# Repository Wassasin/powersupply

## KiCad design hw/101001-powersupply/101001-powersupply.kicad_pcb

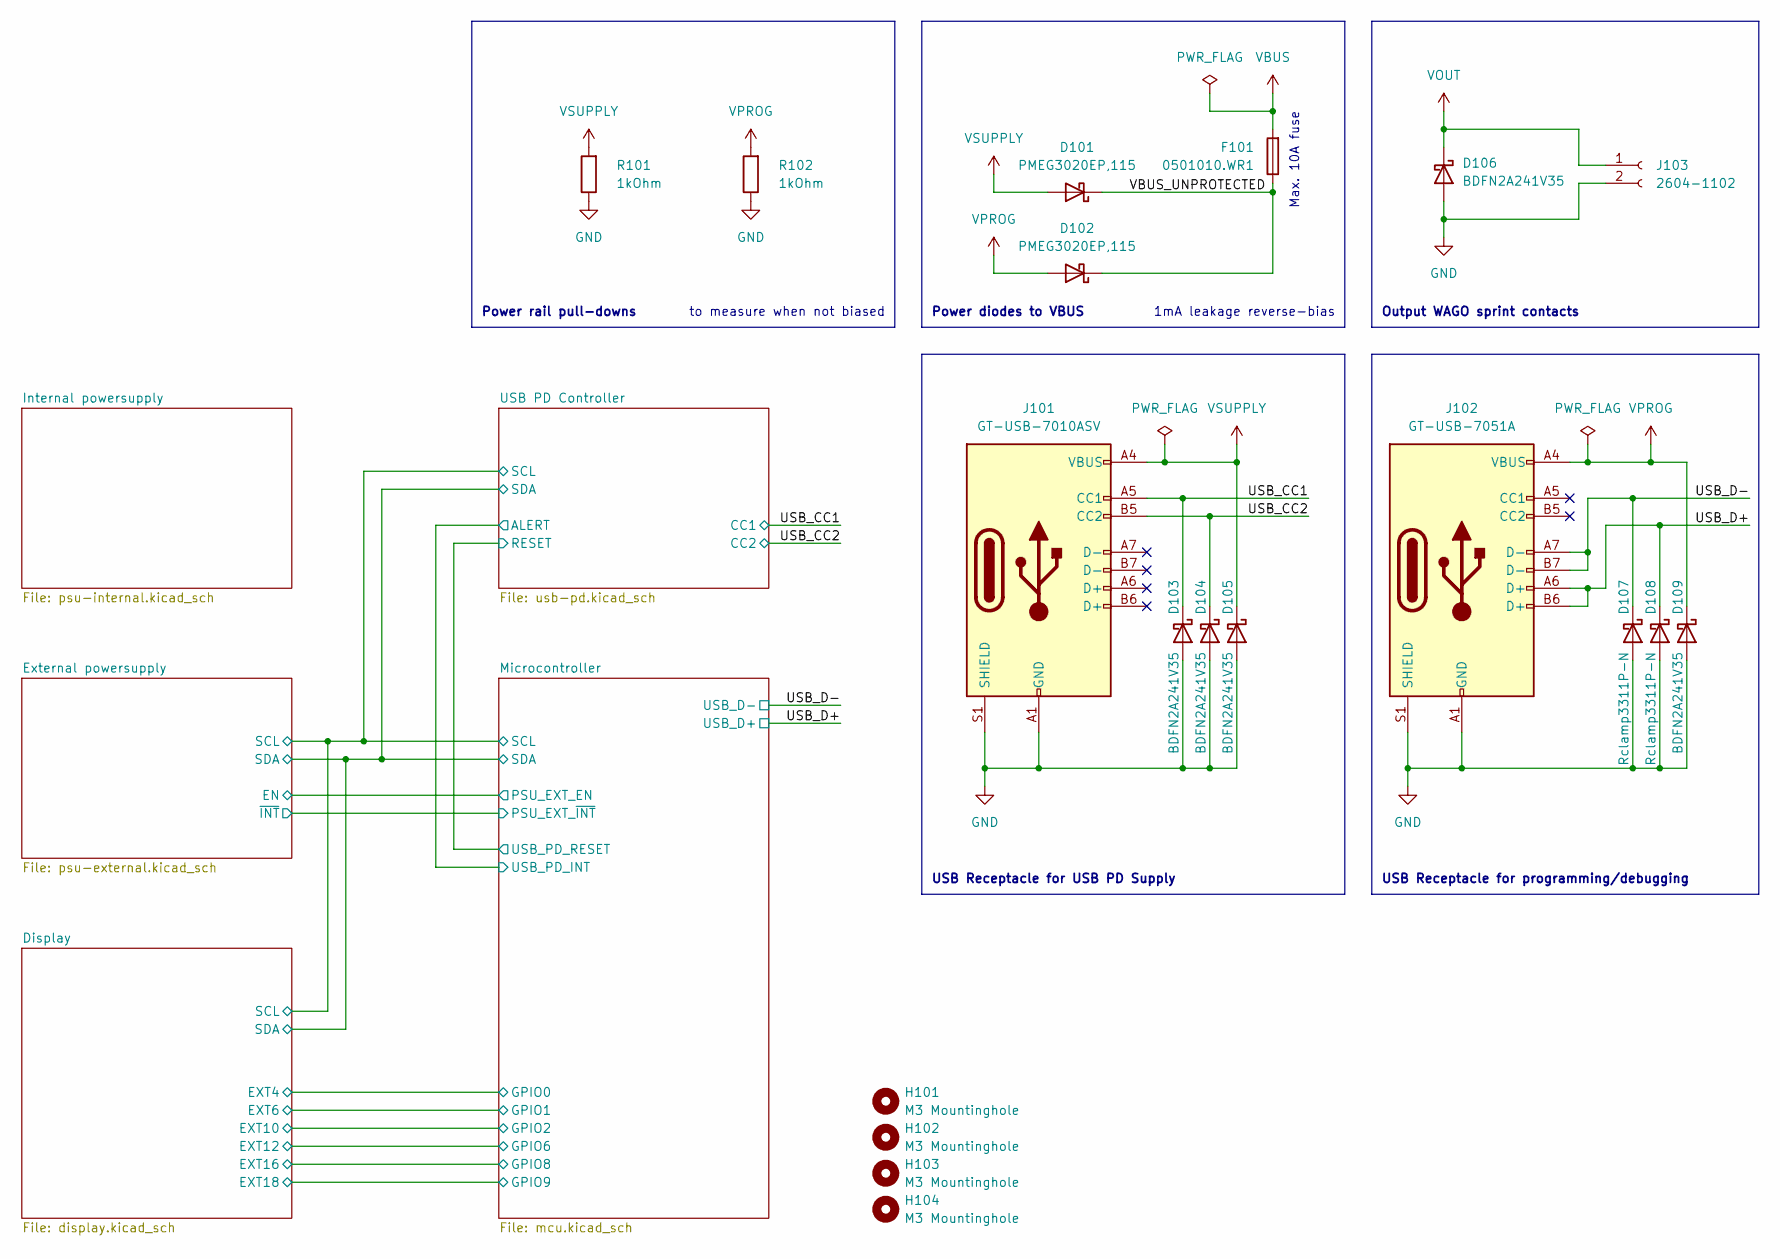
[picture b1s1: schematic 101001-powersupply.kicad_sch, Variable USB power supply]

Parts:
D101, D102: PMEG3020EP,115; D_SOD-128; LCSC C513108
D103, D104, D105, D106, D109: BDFN2A241V35; D_SOD-882; LCSC C406193
D107, D108: Rclamp3311P-N; D_SOD-882; LCSC C406234
F101: 0501010.WR1; Fuse_1206_3216Metric; LCSC C207003
H101, H102, H103, H104: M3 Mountinghole; MountingHole_3.2mm_M3
J101: GT-USB-7010ASV; USB_C_Receptacle_G-Switch_GT-USB-7010ASV; LCSC C2988369
J102: GT-USB-7051A; USB_C_Receptacle_G-Switch_GT-USB-7051x; LCSC C2843970
J103: 2604-1102; WAGO-2604-1102
R101, R102: 1kOhm; R_0402_1005Metric; LCSC C11702

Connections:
/USB_CC1: D103.1 (K), J101.A5 (CC1); also elsewhere on the board
/USB_CC2: D104.1 (K), J101.B5 (CC2); also elsewhere on the board
/USB_D+: D108.1 (K), J102.A6 (D+), J102.B6 (D+); also elsewhere on the board
/USB_D-: D107.1 (K), J102.A7 (D-), J102.B7 (D-); also elsewhere on the board
/VBUS_UNPROTECTED: D101.1 (K), D102.1 (K), F101.1
VBUS: F101.2; also elsewhere on the board
VOUT: D106.1 (K), J103.1; also elsewhere on the board
VPROG: D102.2 (A), D109.1 (K), J102.A4 (VBUS), J102.A9 (VBUS), J102.B4 (VBUS), J102.B9 (VBUS), R102.2; also elsewhere on the board
VSUPPLY: D101.2 (A), D105.1 (K), J101.A4 (VBUS), J101.A9 (VBUS), J101.B4 (VBUS), J101.B9 (VBUS), R101.2; also elsewhere on the board

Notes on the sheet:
to measure when not biased
Max. 10A fuse
Power rail pull-downs
USB Receptacle for programming/debugging
USB Receptacle for USB PD Supply
1mA leakage reverse-bias
Power diodes to VBUS
Output WAGO sprint contacts

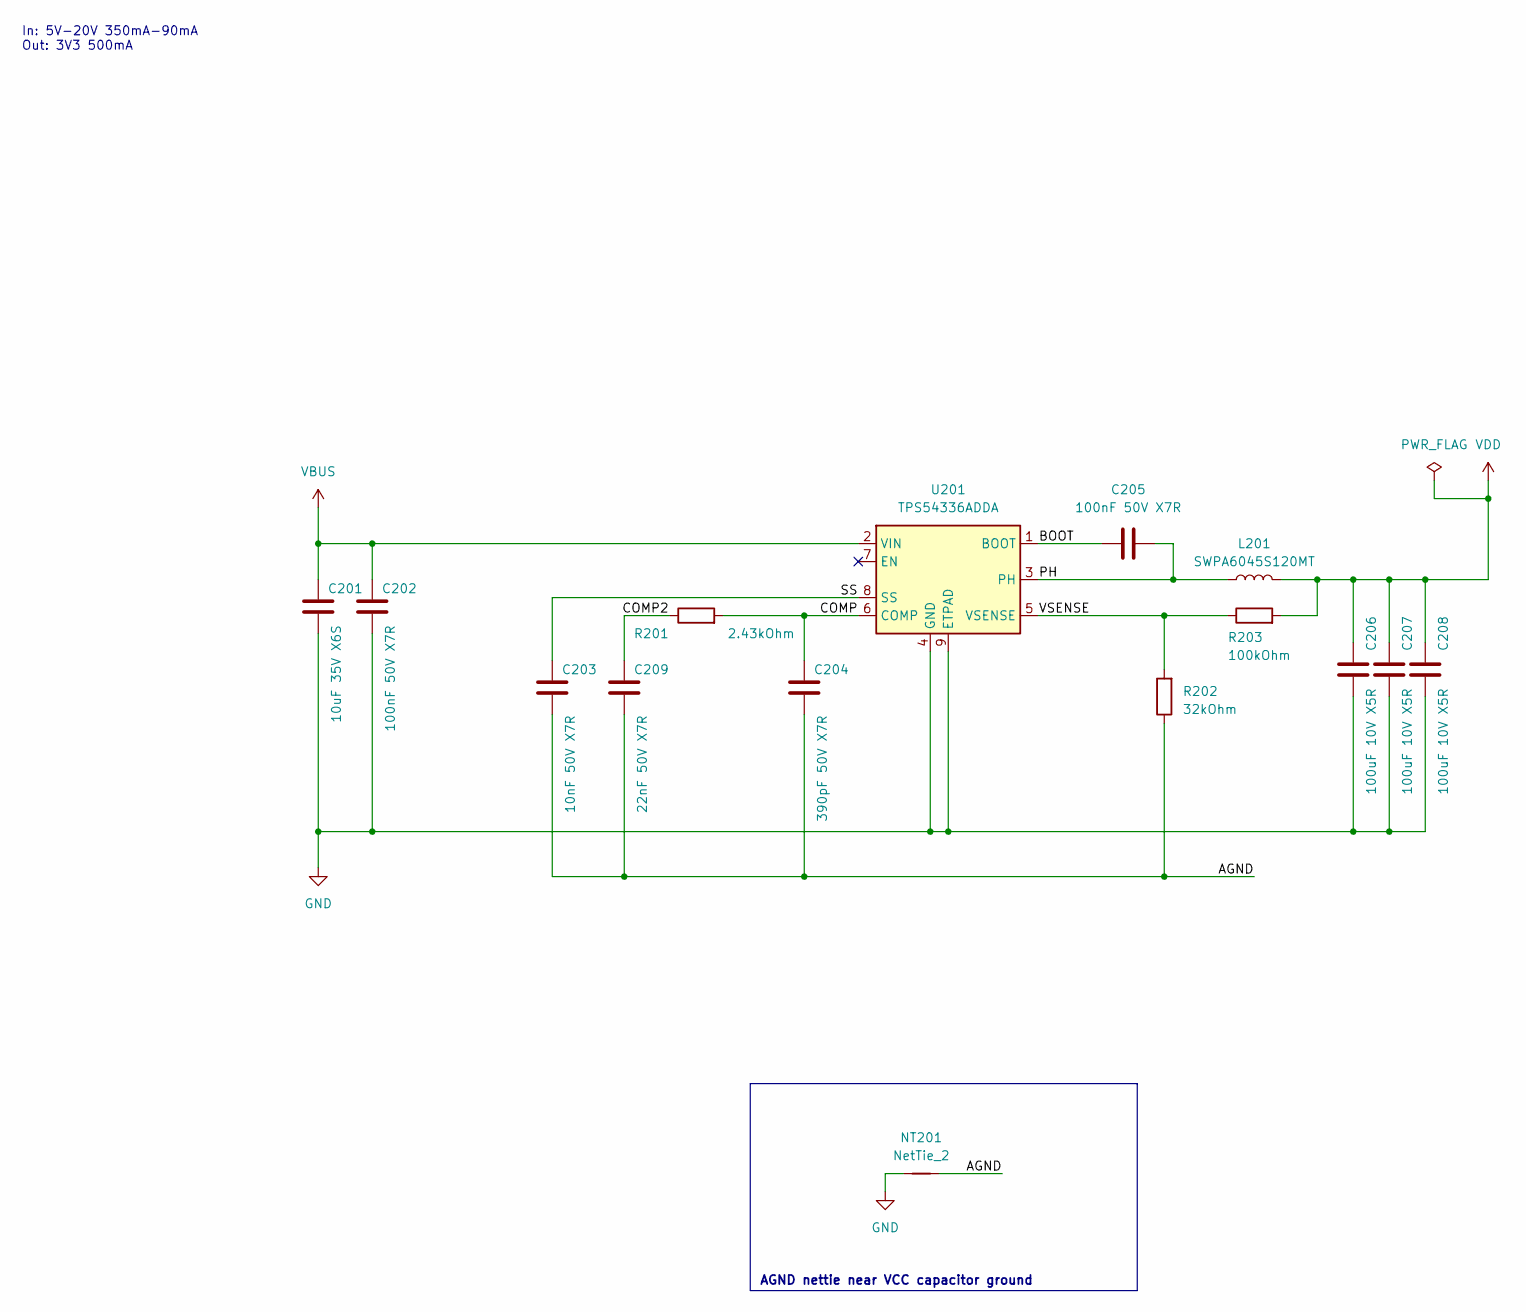
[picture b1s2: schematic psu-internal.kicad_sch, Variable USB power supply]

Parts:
C201: 10uF 35V X6S; C_0805_2012Metric; MPN GRM21BC8YA106KE11L; LCSC C469541
C202, C205: 100nF 50V X7R; C_0402_1005Metric; MPN CL05B104KB54PNC; LCSC C307331
C203: 10nF 50V X7R; C_0402_1005Metric; MPN CL05B103KB5NNNC; LCSC C15195
C204: 390pF 50V X7R; C_0402_1005Metric; MPN CC0402KRX7R9BB391; LCSC C114397
C206, C207, C208: 100uF 10V X5R; C_1206_3216Metric; MPN GRM31CR61A107ME05L; LCSC C312983
C209: 22nF 50V X7R; C_0402_1005Metric; MPN CL05B223KB5NNNC; LCSC C337699
L201: SWPA6045S120MT; L_Sunlord_SWPA6045S; MPN SWPA6045S120MT; LCSC C96951
NT201: NetTie_2; NetTie-2_SMD_Pad0.5mm
R201: 2.43kOhm; R_0402_1005Metric; LCSC C853891
R202: 32kOhm; R_0402_1005Metric; LCSC C11463
R203: 100kOhm; R_0402_1005Metric; LCSC C25741
U201: TPS54336ADDA; TI_SO-PowerPAD-8_ThermalVias; MPN TPS54336ADDA; LCSC C97668

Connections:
/Internal powersupply/AGND: C203.2, C204.2, C209.2, NT201.2, R202.1
/Internal powersupply/BOOT: C205.1, U201.1 (BOOT)
/Internal powersupply/COMP: C204.1, R201.2, U201.6 (COMP)
/Internal powersupply/COMP2: C209.1, R201.1
/Internal powersupply/PH: C205.2, L201.1, U201.3 (PH)
/Internal powersupply/SS: C203.1, U201.8 (SS)
/Internal powersupply/VSENSE: R202.2, R203.1, U201.5 (VSENSE)
VBUS: C201.1, C202.1, U201.2 (VIN); also elsewhere on the board
VDD: C206.1, C207.1, C208.1, L201.2, R203.2; also elsewhere on the board

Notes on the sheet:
In: 5V-20V 350mA-90mA Out: 3V3 500mA
AGND nettie near VCC capacitor ground

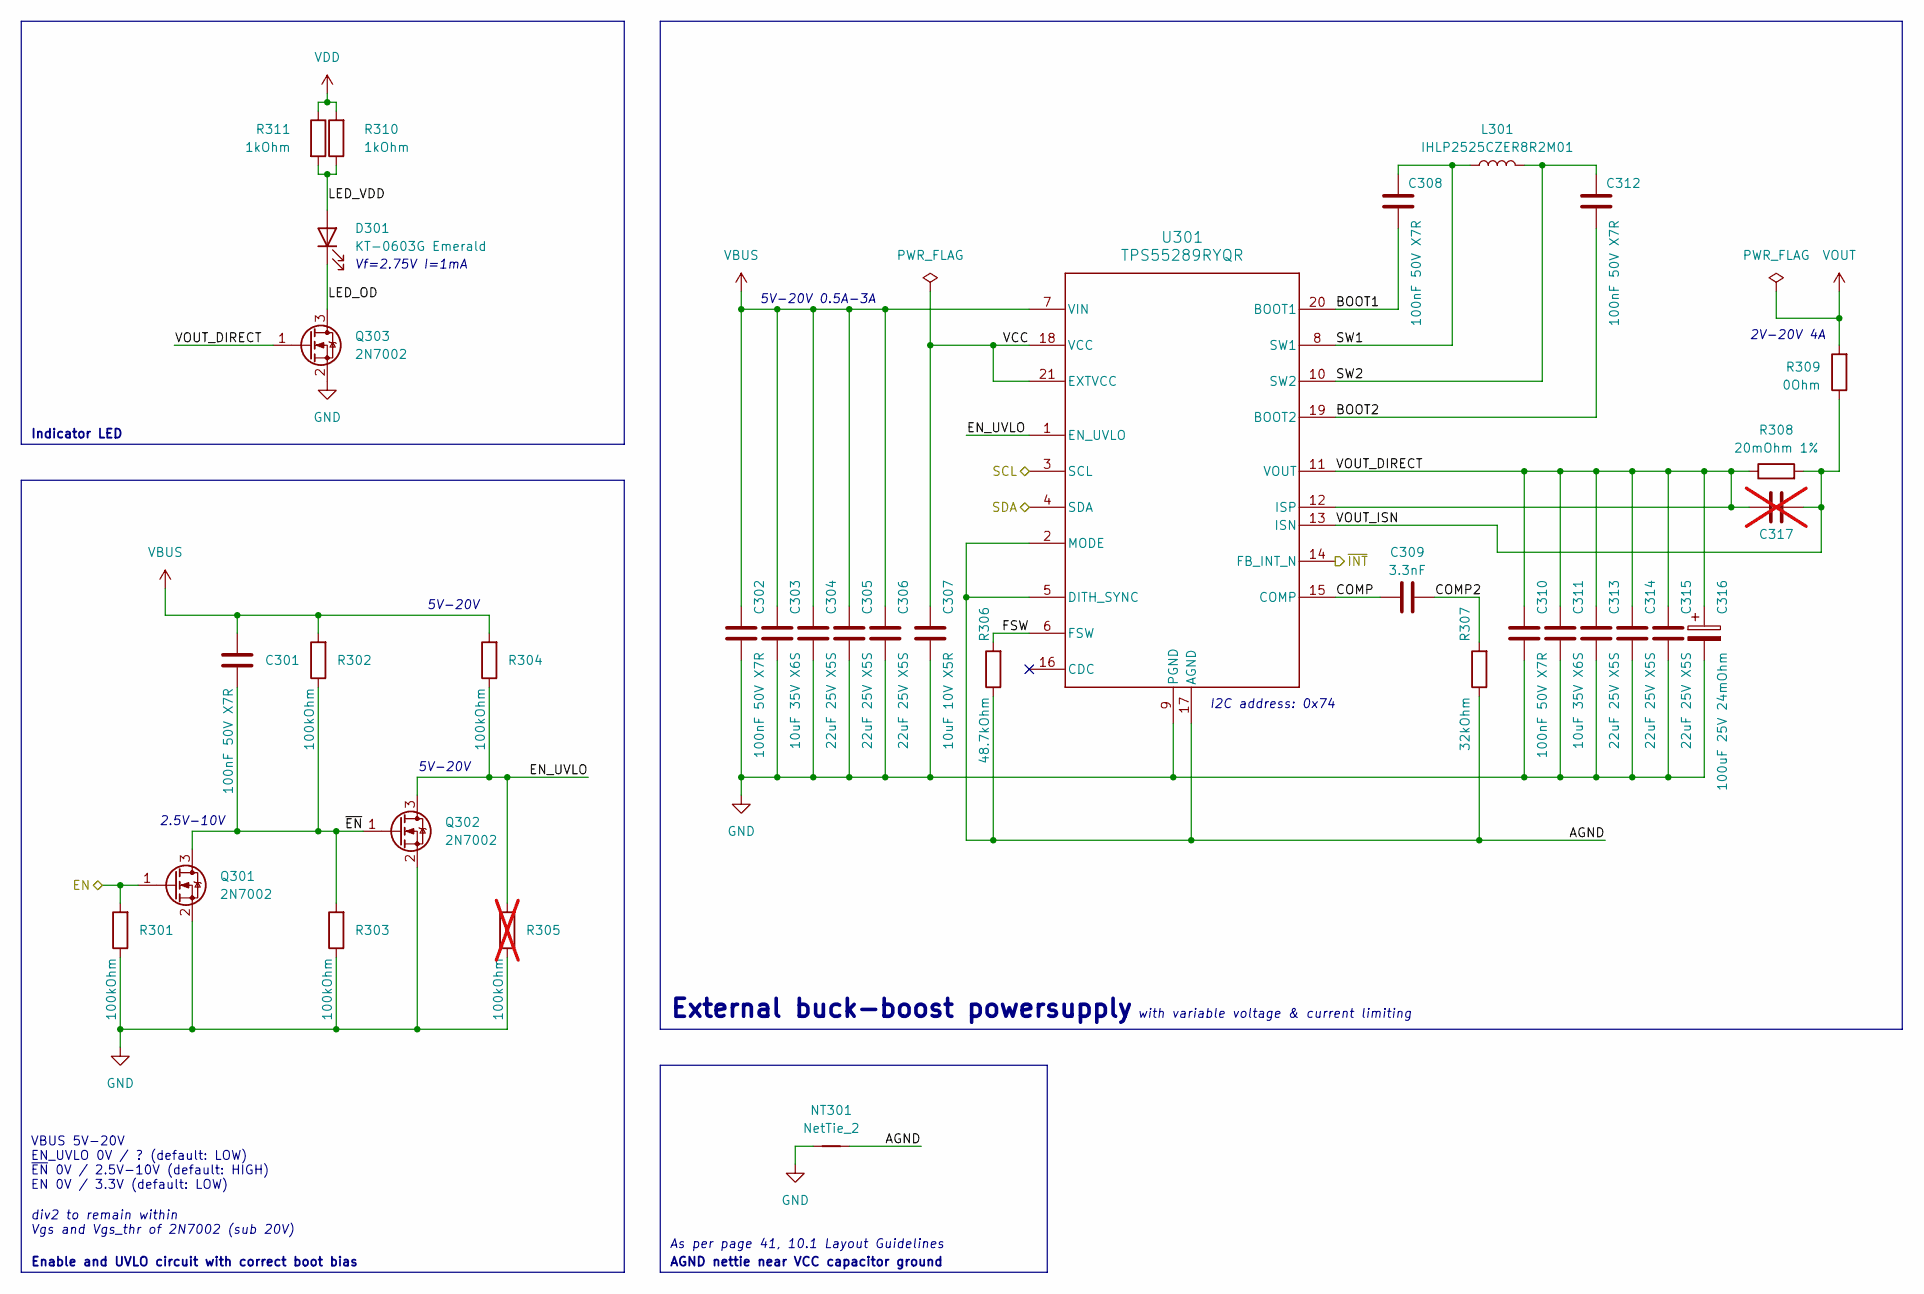
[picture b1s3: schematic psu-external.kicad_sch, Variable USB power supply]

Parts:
C301, C302, C308, C310, C312: 100nF 50V X7R; C_0402_1005Metric; MPN CL05B104KB54PNC; LCSC C307331
C303, C311: 10uF 35V X6S; C_0805_2012Metric; MPN GRM21BC8YA106KE11L; LCSC C469541
C304, C305, C306, C313, C314, C315: 22uF 25V X5S; C_1210_3225Metric; MPN GRM32ER71E226KE15L; LCSC C21397
C307: 10uF 10V X5R; C_0402_1005Metric; MPN GRM155R61A106ME11D; LCSC C408132
C309: 3.3nF; C_0402_1005Metric; MPN CC0402KRX7R9BB332; LCSC C107028
C316: 100uF 25V 24mOhm; CP_Elec_8x6.9; MPN 25SVPF100M; LCSC C136279
C317: C_0402_1005Metric; MPN CL05B104KB54PNC; LCSC C307331; not fitted
D301: KT-0603G Emerald; LED_0603_1608Metric; LCSC C12624
L301: IHLP2525CZER8R2M01; L_Vishay_IHLP-2525; MPN IHLP2525CZER8R2M01; LCSC C506576
NT301: NetTie_2; NetTie-2_SMD_Pad0.5mm
Q301, Q302, Q303: 2N7002; SOT-23; LCSC C8545
R301, R302, R303, R304: 100kOhm; R_0402_1005Metric; LCSC C25741
R305: 100kOhm; R_0402_1005Metric; LCSC C25741; not fitted
R306: 48.7kOhm; R_0402_1005Metric; LCSC C26981
R307: 32kOhm; R_0402_1005Metric; LCSC C11463
R308: 20mOhm 1%; R_2512_6332Metric; LCSC C2903469
R309: 0Ohm; R_2512_6332Metric; LCSC C25469
R310, R311: 1kOhm; R_0402_1005Metric; LCSC C11702
U301: TPS55289RYQR; Texas_RYQ0021A_VQFN-21_P0.5mm_EP5.0x3.0mm

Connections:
/Display/SCL: U301.3 (SCL); also elsewhere on the board
/Display/SDA: U301.4 (SDA); also elsewhere on the board
/External powersupply/AGND: NT301.2, R306.1, R307.1, U301.2 (MODE), U301.5 (DITH_SYNC), U301.17 (AGND)
/External powersupply/BOOT1: C308.2, U301.20 (BOOT1)
/External powersupply/BOOT2: C312.2, U301.19 (BOOT2)
/External powersupply/COMP: C309.1, U301.15 (COMP)
/External powersupply/COMP2: C309.2, R307.2
/External powersupply/EN: Q301.1 (G), R301.2; also elsewhere on the board
/External powersupply/EN_UVLO: Q302.3 (D), R304.1, R305.2, U301.1 (EN_UVLO)
/External powersupply/FSW: R306.2, U301.6 (FSW)
/External powersupply/LED_OD: D301.1 (K), Q303.3 (D)
/External powersupply/LED_VDD: D301.2 (A), R310.1, R311.2
/External powersupply/SW1: C308.1, L301.1, U301.8 (SW1)
/External powersupply/SW2: C312.1, L301.2, U301.10 (SW2)
/External powersupply/VCC: C307.1, U301.18 (VCC), U301.21 (EXTVCC)
/External powersupply/VOUT_DIRECT: C310.1, C311.1, C313.1, C314.1, C315.1, C316.1, C317.1, Q303.1 (G), R308.1, U301.11 (VOUT), U301.12 (ISP)
/External powersupply/VOUT_ISN: C317.2, R308.2, R309.1, U301.13 (ISN)
/External powersupply/~EN: C301.2, Q301.3 (D), Q302.1 (G), R302.1, R303.2
/External powersupply/~INT: U301.14 (FB_INT_N); also elsewhere on the board
VBUS: C301.1, C302.1, C303.1, C304.1, C305.1, C306.1, R302.2, R304.2, U301.7 (VIN); also elsewhere on the board
VDD: R310.2, R311.1; also elsewhere on the board
VOUT: R309.2; also elsewhere on the board

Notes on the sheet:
div2 to remain within Vgs and Vgs_thr of 2N7002 (sub 20V)
with variable voltage & current limiting
Vf=2.75V I=1mA
5V-20V
I2C address: 0x74
VBUS 5V-20V EN_UVLO 0V / ? (default: LOW) ~{EN} 0V / 2.5V-10V (default: HIGH) EN 0V / 3.3V (default: LOW)
As per page 41, 10.1 Layout Guidelines
Indicator LED
2.5V-10V
2V-20V 4A
5V-20V 0.5A-3A
AGND nettie near VCC capacitor ground
Enable and UVLO circuit with correct boot bias
External buck-boost powersupply

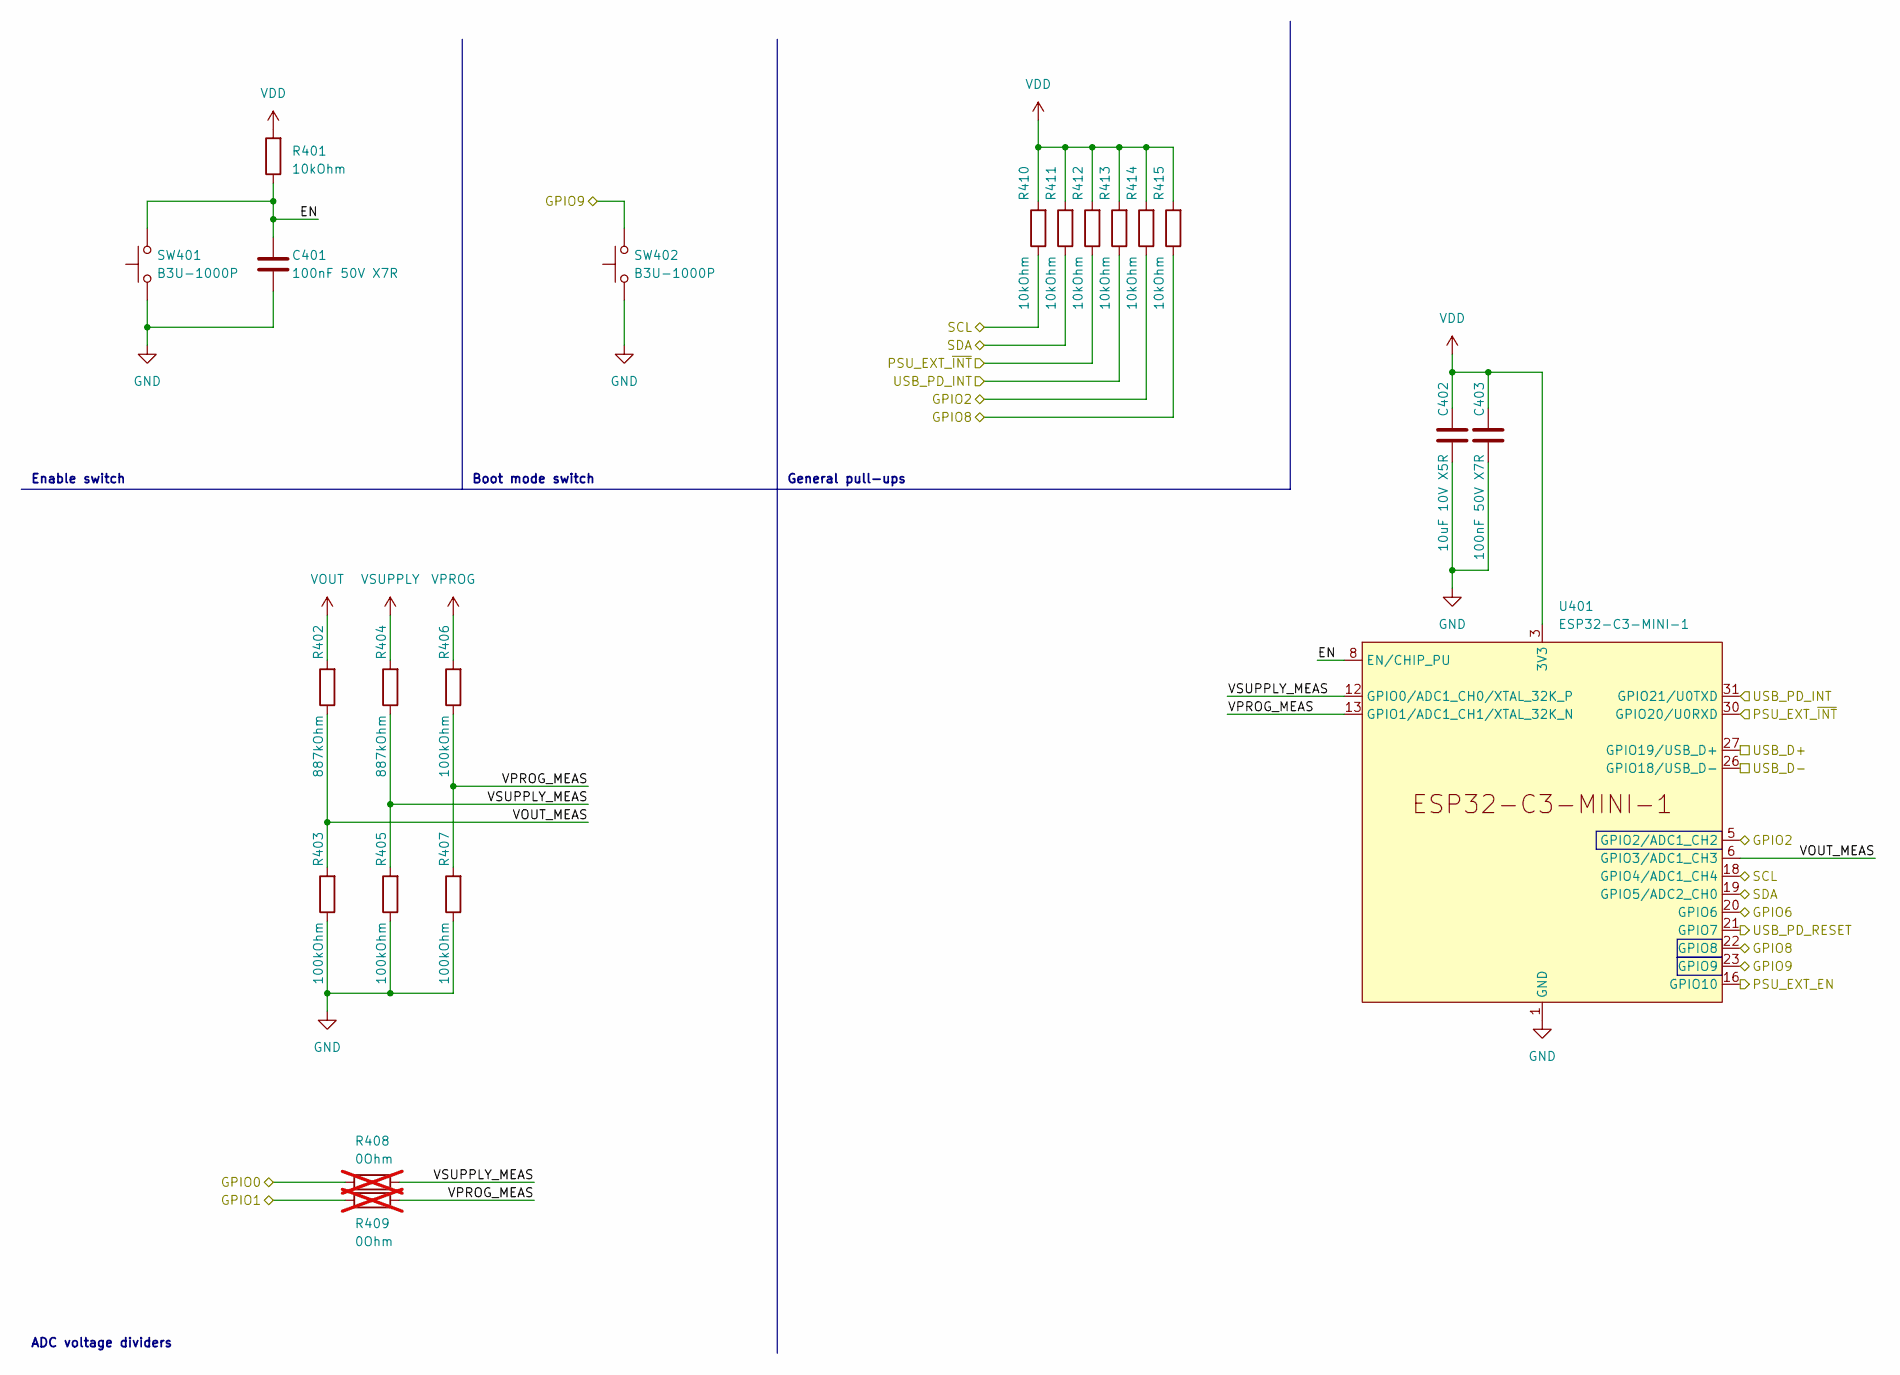
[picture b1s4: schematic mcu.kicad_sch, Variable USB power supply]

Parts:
C401, C403: 100nF 50V X7R; C_0402_1005Metric; MPN CL05B104KB54PNC; LCSC C307331
C402: 10uF 10V X5R; C_0402_1005Metric; MPN GRM155R61A106ME11D; LCSC C408132
R401, R410, R411, R412, R413, R414, R415: 10kOhm; R_0402_1005Metric; LCSC C60490
R402, R404: 887kOhm; R_0402_1005Metric; LCSC C137930
R403, R405, R406, R407: 100kOhm; R_0402_1005Metric; LCSC C25741
R408, R409: 0Ohm; R_0402_1005Metric; not fitted
SW401, SW402: B3U-1000P; SW_SPST_B3U-1000P; LCSC C231329
U401: ESP32-C3-MINI-1

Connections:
/Display/EXT4: R408.1; also elsewhere on the board
/Display/EXT6: R409.2; also elsewhere on the board
/Display/EXT10: R414.1, U401.5 (GPIO2/ADC1_CH2); also elsewhere on the board
/Display/EXT12: U401.20 (GPIO6); also elsewhere on the board
/Display/EXT16: R415.1, U401.22 (GPIO8); also elsewhere on the board
/Display/EXT18: SW402.2, U401.23 (GPIO9); also elsewhere on the board
/Display/SCL: R410.1, U401.18 (GPIO4/ADC1_CH4); also elsewhere on the board
/Display/SDA: R411.1, U401.19 (GPIO5/ADC2_CH0); also elsewhere on the board
/External powersupply/EN: U401.16 (GPIO10); also elsewhere on the board
/External powersupply/~INT: R412.1, U401.30 (GPIO20/U0RXD); also elsewhere on the board
/Microcontroller/EN: C401.2, R401.1, SW401.2, U401.8 (EN/CHIP_PU)
/Microcontroller/USB_PD_INT: R413.1, U401.31 (GPIO21/U0TXD); also elsewhere on the board
/Microcontroller/USB_PD_RESET: U401.21 (GPIO7); also elsewhere on the board
/Microcontroller/VOUT_MEAS: R402.1, R403.2, U401.6 (GPIO3/ADC1_CH3)
/Microcontroller/VPROG_MEAS: R406.1, R407.2, R409.1, U401.13 (GPIO1/ADC1_CH1/XTAL_32K_N)
/Microcontroller/VSUPPLY_MEAS: R404.1, R405.2, R408.2, U401.12 (GPIO0/ADC1_CH0/XTAL_32K_P)
/USB_D+: U401.27 (GPIO19/USB_D+); also elsewhere on the board
/USB_D-: U401.26 (GPIO18/USB_D-); also elsewhere on the board
VDD: C402.1, C403.1, R401.2, R410.2, R411.2, R412.2, R413.2, R414.2, R415.2, U401.3 (3V3); also elsewhere on the board
VOUT: R402.2; also elsewhere on the board
VPROG: R406.2; also elsewhere on the board
VSUPPLY: R404.2; also elsewhere on the board

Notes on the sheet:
Enable switch
ADC voltage dividers
General pull-ups
Boot mode switch

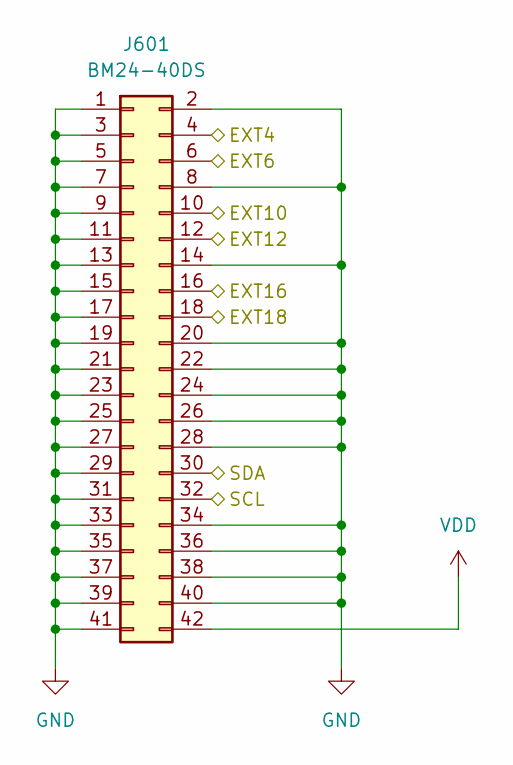
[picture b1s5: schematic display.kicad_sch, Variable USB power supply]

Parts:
J601: BM24-40DS; Hirose_BM24_BM24-40DS-2-0.35V_2x20_P0.35mm_PowerPin2_Vertic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; MPN BM24-40DS/2-0.35V(51); LCSC C424559

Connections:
/Display/EXT4: J601.4; also elsewhere on the board
/Display/EXT6: J601.6; also elsewhere on the board
/Display/EXT10: J601.10; also elsewhere on the board
/Display/EXT12: J601.12; also elsewhere on the board
/Display/EXT16: J601.16; also elsewhere on the board
/Display/EXT18: J601.18; also elsewhere on the board
/Display/SCL: J601.32; also elsewhere on the board
/Display/SDA: J601.30; also elsewhere on the board
VDD: J601.42; also elsewhere on the board

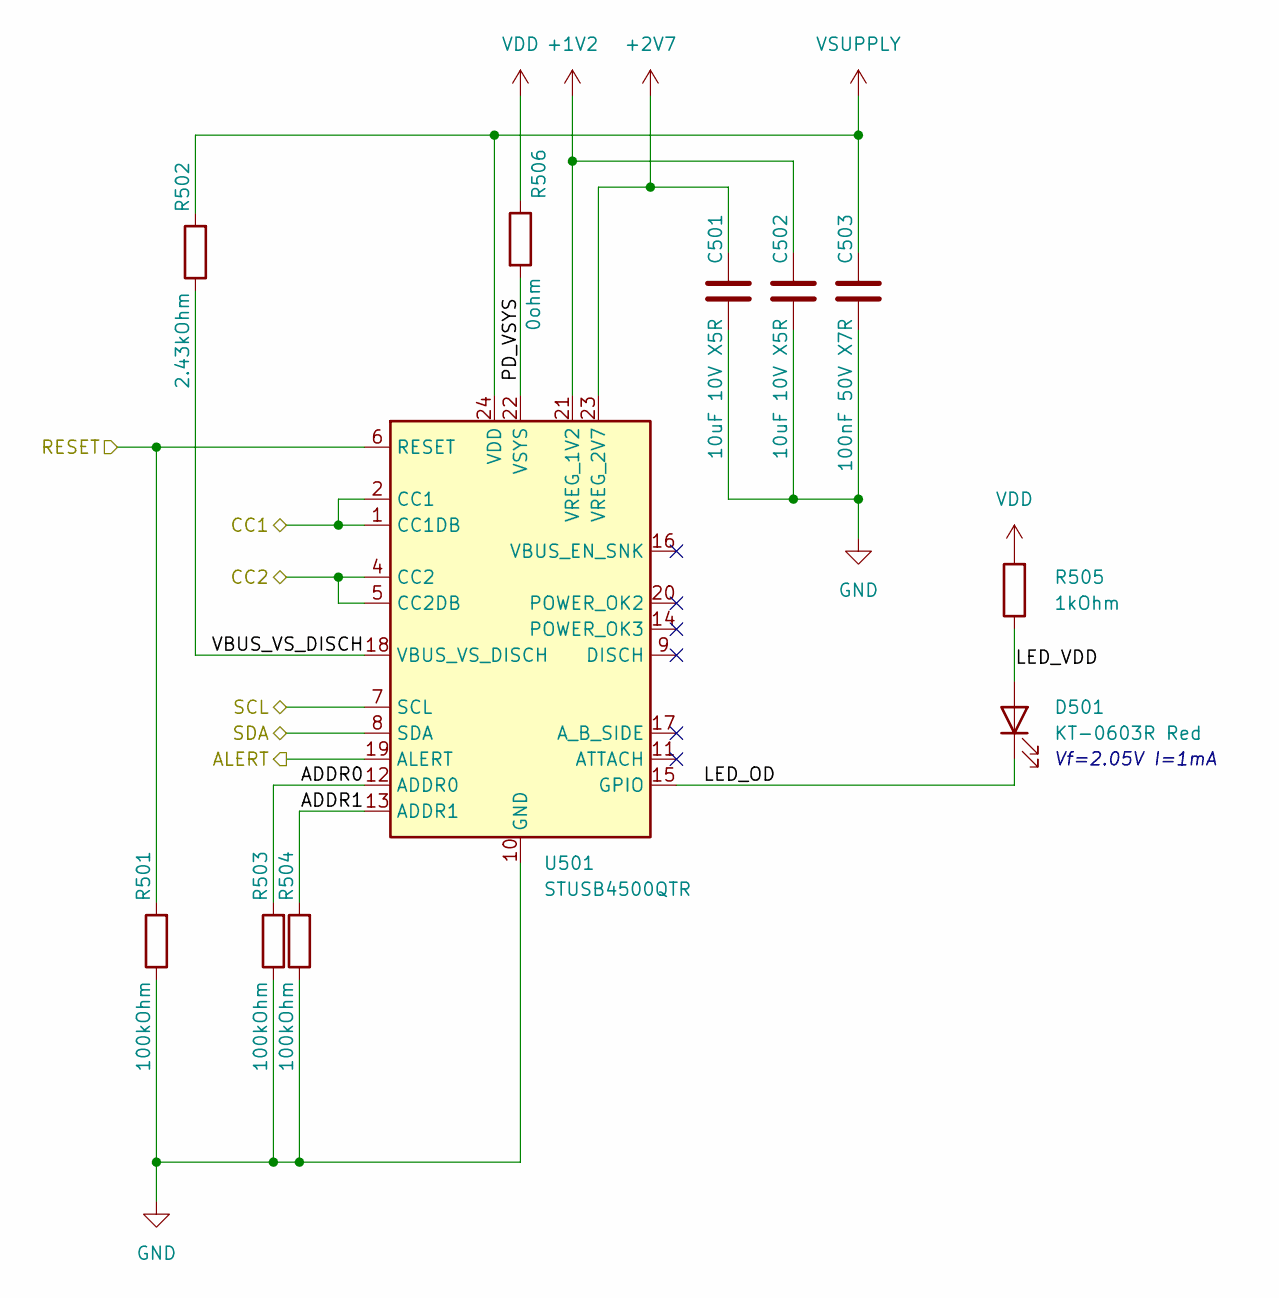
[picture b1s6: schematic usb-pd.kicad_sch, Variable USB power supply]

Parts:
C501, C502: 10uF 10V X5R; C_0402_1005Metric; MPN GRM155R61A106ME11D; LCSC C408132
C503: 100nF 50V X7R; C_0402_1005Metric; MPN CL05B104KB54PNC; LCSC C307331
D501: KT-0603R Red; LED_0603_1608Metric; LCSC C2286
R501, R503, R504: 100kOhm; R_0402_1005Metric; LCSC C25741
R502: 2.43kOhm; R_0402_1005Metric; LCSC C853891
R505: 1kOhm; R_0402_1005Metric; LCSC C11702
R506: 0ohm; R_0402_1005Metric; LCSC C2906877
U501: STUSB4500QTR; QFN-24-1EP_4x4mm_P0.5mm_EP2.7x2.7mm; LCSC C2678061

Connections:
+1V2: C502.1, U501.21 (VREG_1V2)
+2V7: C501.1, U501.23 (VREG_2V7)
/Display/SCL: U501.7 (SCL); also elsewhere on the board
/Display/SDA: U501.8 (SDA); also elsewhere on the board
/Microcontroller/USB_PD_INT: U501.19 (ALERT); also elsewhere on the board
/Microcontroller/USB_PD_RESET: R501.2, U501.6 (RESET); also elsewhere on the board
/USB PD Controller/ADDR0: R503.2, U501.12 (ADDR0)
/USB PD Controller/ADDR1: R504.2, U501.13 (ADDR1)
/USB PD Controller/LED_OD: D501.1 (K), U501.15 (GPIO)
/USB PD Controller/LED_VDD: D501.2 (A), R505.1
/USB PD Controller/VBUS_VS_DISCH: R502.1, U501.18 (VBUS_VS_DISCH)
/USB_CC1: U501.1 (CC1DB), U501.2 (CC1); also elsewhere on the board
/USB_CC2: U501.4 (CC2), U501.5 (CC2DB); also elsewhere on the board
VDD: R505.2, R506.1; also elsewhere on the board
VSUPPLY: C503.1, R502.2, U501.24 (VDD); also elsewhere on the board

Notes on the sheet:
Vf=2.05V I=1mA

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
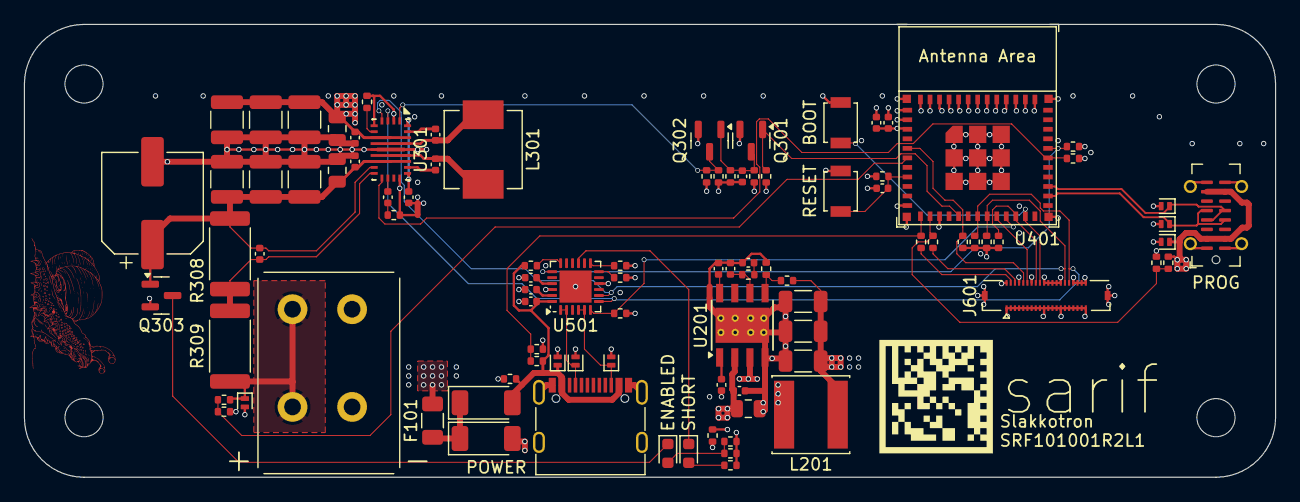
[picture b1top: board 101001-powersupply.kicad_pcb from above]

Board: 6 copper layers, 105.0 x 38.0 mm, 101 parts (0 on the bottom side), 56 nets.

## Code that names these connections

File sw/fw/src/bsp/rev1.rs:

use crate::executors::interrupt::InterruptExecutor;

use embassy_embedded_hal::shared_bus::asynch::i2c::I2cDevice;
use embassy_executor::SendSpawner;
use embassy_sync::{
    blocking_mutex::raw::{CriticalSectionRawMutex, NoopRawMutex},
    mutex::Mutex,
};
use embedded_hal_async::i2c;
use esp_hal::{
    analog::adc::{Adc, AdcCalBasic, AdcCalCurve, AdcConfig, AdcPin},
    clock::{ClockControl, Clocks},
    delay::Delay,
    dma::{ChannelCreator, Dma, DmaPriority},
    dma_buffers,
    gpio::{GpioPin, Input, Io, Level, Output, Pull},
    i2c::I2C,
    i2s::{DataFormat, I2s, Standard},
    ledc::{timer::Timer, LSGlobalClkSource, Ledc, LowSpeed},
    peripherals::{Peripherals, ADC1, I2C0, TIMG1},
    prelude::*,
    rmt::Rmt,
    rng::Rng,
    rtc_cntl::Rtc,
    system::SystemControl,
    timer::{
        systimer::SystemTimer,
        timg::{TimerGroup, Wdt},
    },
    Async, Blocking,
};
use esp_storage::FlashStorage;
use esp_wifi::wifi::{WifiController, WifiDevice, WifiStaDevice};
use static_cell::StaticCell;

pub type I2cInstance = I2C<'static, I2C0, Async>;
pub type ClocksInstance = Clocks<'static>;

pub type I2cBus = Mutex<CriticalSectionRawMutex, I2cInstance>;
pub type I2cBusDevice = I2cDevice<'static, CriticalSectionRawMutex, I2cInstance>;
pub type I2cError = <I2cBusDevice as i2c::ErrorType>::Error;

pub struct Wifi {
    pub device: WifiDevice<'static, WifiStaDevice>,
    pub controller: WifiController<'static>,
    pub seed: u64,
}

pub type StatsADCInstance = ADC1;
pub type StatsAdcCal = AdcCalCurve<StatsADCInstance>;
pub type StatsVProgMeasurePin = AdcPin<GpioPin<1>, StatsADCInstance, StatsAdcCal>;
pub type StatsVSupplyMeasurePin = AdcPin<GpioPin<0>, StatsADCInstance, StatsAdcCal>;
pub type StatsVOutMeasurePin = AdcPin<GpioPin<3>, StatsADCInstance, StatsAdcCal>;

pub struct StatsPins {
    pub vprog: StatsVProgMeasurePin,
    pub vsupply: StatsVSupplyMeasurePin,
    pub vout: StatsVOutMeasurePin,
}

pub type StatsAdc = Adc<'static, StatsADCInstance>;

pub struct Stats {
    pub pins: StatsPins,
    pub adc: StatsAdc,
}

pub type PowerExtEnablePin = Output<'static, GpioPin<10>>;
pub type PowerExtNIntPin = Input<'static, GpioPin<20>>;

pub struct PowerExt {
    pub i2c: I2cBusDevice,
    pub enable_pin: PowerExtEnablePin,
    pub nint_pin: PowerExtNIntPin,
}

pub type USBPDResetPin = Output<'static, GpioPin<7>>;
pub type USBPDIntPin = Input<'static, GpioPin<21>>;

pub struct Usbpd {
    pub reset_pin: USBPDResetPin,
    pub int_pin: USBPDIntPin,
    pub i2c: I2cBusDevice,
}

pub struct Watchdog {
    pub peri: Wdt<TIMG1, Async>,
}

pub struct Bsp {
    pub i2c_bus: &'static I2cBus,

    pub clocks: &'static ClocksInstance,
    pub delay: Delay,
    pub rtc: Rtc<'static>,
    pub wifi: Wifi,
    pub stats: Stats,
    pub power_ext: PowerExt,
    pub usb_pd: Usbpd,
    pub watchdog: Watchdog,

    pub high_prio_spawner: SendSpawner,
}

impl Bsp {
    pub fn init(peripherals: Peripherals) -> Self {
        let system = SystemControl::new(peripherals.SYSTEM);
        let io = Io::new(peripherals.GPIO, peripherals.IO_MUX);

        // Set device speed
        let clocks = {
            static CLOCKS: StaticCell<Clocks> = StaticCell::new();
            CLOCKS.init(ClockControl::max(system.clock_control).freeze())
        };

        // Initialize the RTC before the Wifi because of esp-wifi issues
        let mut rtc = Rtc::new(peripherals.LPWR, None);

        // Wifi
        let wifi = {
            let systimer = SystemTimer::new(peripherals.SYSTIMER).alarm0;
            let mut rng = Rng::new(peripherals.RNG);
            let wifi_seed = (rng.random() as u64) << 32 | rng.random() as u64;
            let wifi_init = esp_wifi::initialize(
                esp_wifi::EspWifiInitFor::Wifi,
                systimer,
                rng,
                peripherals.RADIO_CLK,
                clocks,
            )
            .unwrap();

            let (wifi_device, wifi_controller) =
                esp_wifi::wifi::new_with_mode(&wifi_init, peripherals.WIFI, WifiStaDevice).unwrap();

            Wifi {
                device: wifi_device,
                controller: wifi_controller,
                seed: wifi_seed,
            }
        };

        // Initialize embassy
        {
            let timg0 = TimerGroup::new_async(peripherals.TIMG0, clocks);
            esp_hal_embassy::init(clocks, timg0);
        }

        // I2C generic bus
        let i2c_bus: &'static _ = {
            let i2c: I2cInstance = I2C::new_with_timeout_async(
                peripherals.I2C0,
                io.pins.gpio5,
                io.pins.gpio4,
                400u32.kHz(),
                clocks,
                Some(20),
            );

            static I2C_BUS: StaticCell<I2cBus> = StaticCell::new();
            I2C_BUS.init(Mutex::new(i2c))
        };

        let stats = {
            let vprog = io.pins.gpio1;
            let vsupply = io.pins.gpio0;
            let vout = io.pins.gpio3;

            let mut adc_config = AdcConfig::new();
            let vprog = adc_config.enable_pin_with_cal::<_, StatsAdcCal>(
                vprog,
                esp_hal::analog::adc::Attenuation::Attenuation11dB,
            );
            let vsupply = adc_config.enable_pin_with_cal::<_, StatsAdcCal>(
                vsupply,
                esp_hal::analog::adc::Attenuation::Attenuation11dB,
            );
            let vout = adc_config.enable_pin_with_cal::<_, StatsAdcCal>(
                vout,
                esp_hal::analog::adc::Attenuation::Attenuation11dB,
            );
            let adc = Adc::new(peripherals.ADC1, adc_config);

            Stats {
                adc,
                pins: StatsPins {
                    vprog,
                    vsupply,
                    vout,
                },
            }
        };

        let power_ext = PowerExt {
            i2c: I2cBusDevice::new(i2c_bus),
            enable_pin: Output::new(io.pins.gpio10, Level::Low),
            nint_pin: Input::new(io.pins.gpio20, Pull::None),
        };

        let usb_pd = Usbpd {
            reset_pin: Output::new(io.pins.gpio7, Level::Low),
            int_pin: Input::new(io.pins.gpio21, Pull::None),
            i2c: I2cBusDevice::new(i2c_bus),
        };

        let watchdog = {
            let timg1 = TimerGroup::new_async(peripherals.TIMG1, clocks);
            Watchdog { peri: timg1.wdt }
        };

        let mut delay = Delay::new(clocks);

        static EXECUTOR: StaticCell<InterruptExecutor<2>> = StaticCell::new();
        let executor =
            InterruptExecutor::new(system.software_interrupt_control.software_interrupt2);
        let executor = EXECUTOR.init(executor);

        let high_prio_spawner = executor.start(esp_hal::interrupt::Priority::Priority3);

        log::info!("initialized");

        Bsp {
            i2c_bus,
            clocks,
            delay,
            rtc,
            wifi,
            stats,
            power_ext,
            usb_pd,
            watchdog,
            high_prio_spawner,
        }
    }
}

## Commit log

2024-04-23 Added initial sketch
2024-04-23 Progress on board design
2024-04-24 Finalized board design
2024-06-19 Fixed Ccomp
2024-06-19 Added strapping pins bias and buttons
2024-06-20 Added initial firmware
2024-06-20 Emit stats
2024-06-21 Moved to serde_json_core
2024-06-24 Added TPS55289 driver
2024-06-24 Implemented OCP
2024-06-24 Added TPS55289 vref computation
2024-06-25 Added USB PD stub
2024-06-26 WIP USB PD
2024-06-26 Added iout limit
2024-06-27 Added multiprio
2024-06-27 WIP storage
2024-06-27 Hardware improvements
2024-07-02 Simple storage working
2024-07-02 Implemented record push
2024-07-02 Make power_ext use configuration system
2024-07-03 Fix USB-PD with no programmer connection
2024-07-03 Added events system
2024-07-03 Updated dependencies
2024-07-03 Emit the vout state to MQTT
2024-07-03 Implemented setting configs
2024-07-03 Fixed clippy issues; added backoff propagation
2024-07-04 Added watchdog
2024-07-04 Added timestamp to logs
2024-07-04 WIP executor
2024-07-04 Added fork of executor to keep track of idle time
2024-07-10 Made usb-pd up more reliable
2024-07-10 Made netcode more robust
